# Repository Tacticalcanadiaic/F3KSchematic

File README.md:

# F3KSchematic
Schematic for ESP32-S3 flight unit for F3K

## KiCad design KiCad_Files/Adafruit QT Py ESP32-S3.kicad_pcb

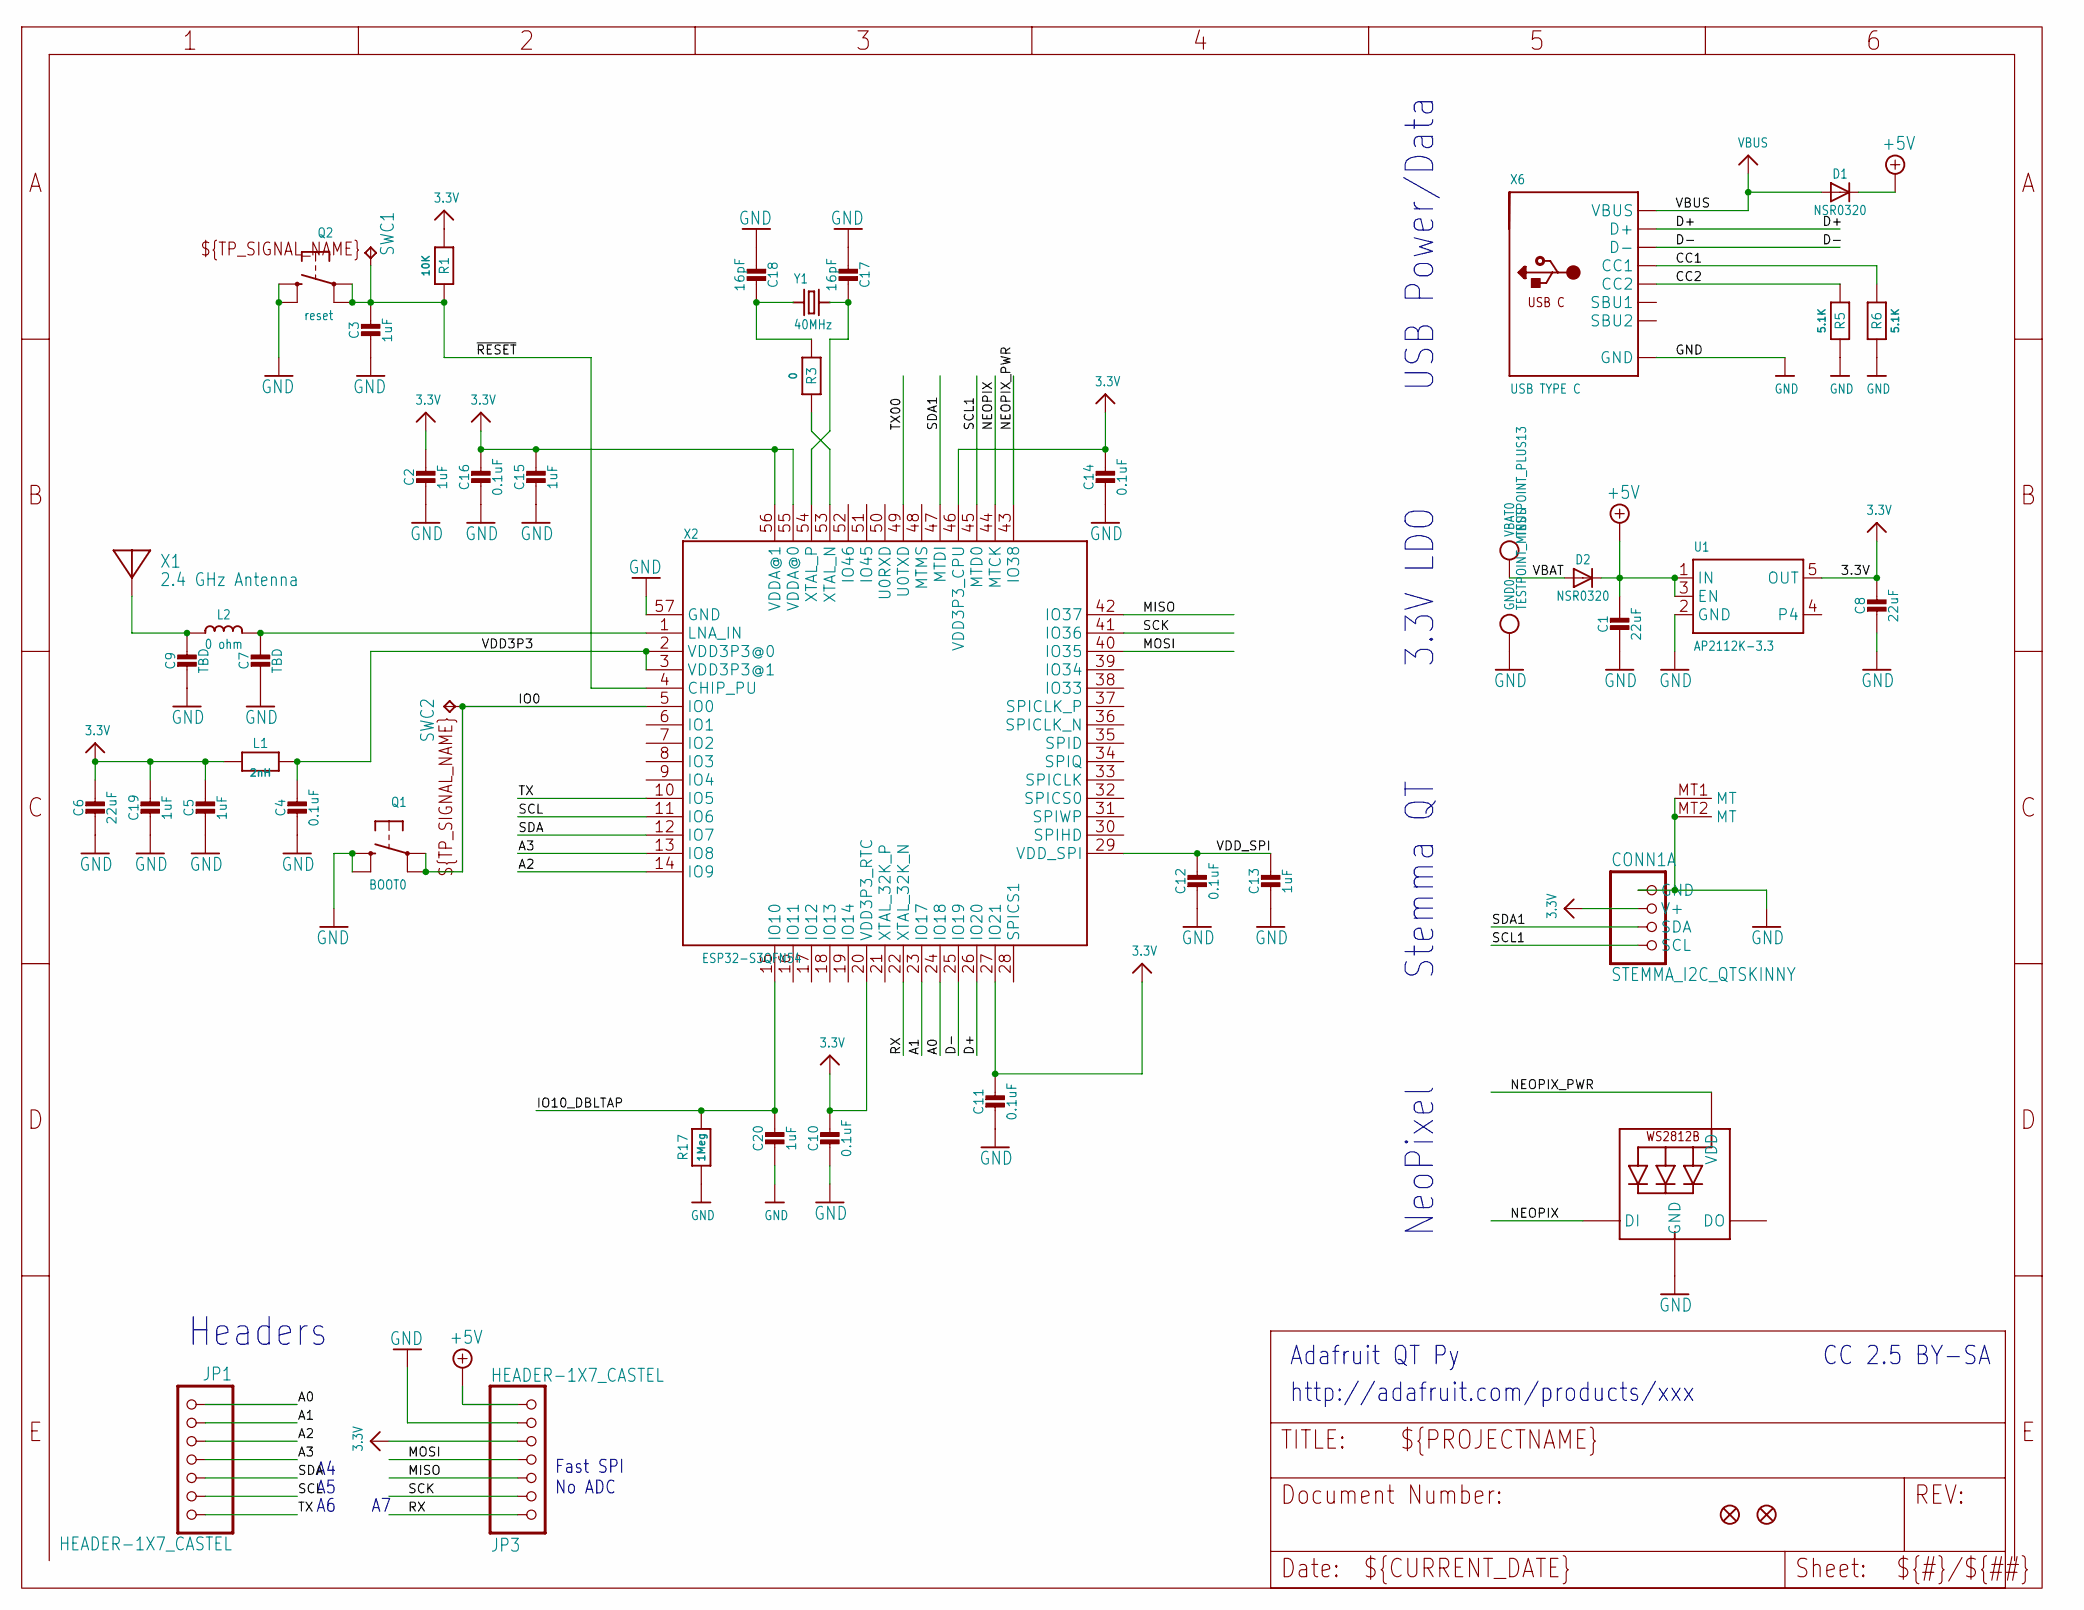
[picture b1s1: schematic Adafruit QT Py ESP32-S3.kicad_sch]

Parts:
C1, C6, C8: 22uF; 0805-NO
C2, C3, C5, C13, C15, C19, C20: 1uF; _0402NO
C4, C10, C11, C12, C14, C16: 0.1uF; _0402NO
C7, C9: TBD; _0402NO
C17, C18: 16pF; _0402NO
CONN1: STEMMA_I2C_QTSKINNY; JST_SH4_SKINNY
D1, D2: NSR0320; SOD-323_MINI
GND0: TESTPOINT_MINUS; TESTPOINT_MINUS_1X3MM
JP1, JP3: HEADER-1X7_CASTEL; 1X07_CASTEL
L1: 2nH; _0402NO
L2: 0 ohm; _0402
LED1: WS2812B_SK6805_1515; SK6805_1515
Q1: BOOT0; BTN_KMR2_4.6X2.8
Q2: reset; BTN_KMR2_4.6X2.8
R1: 10K; _0402NO
R3: 0; _0402NO
R5, R6: 5.1K; _0402NO
R17: 1Meg; _0402NO
SWC1, SWC2: TPB1,27; B1,27
U1: AP2112K-3.3; SOT23-5
U$6, U$8: FIDUCIAL_1MM
VBAT0: TESTPOINT_PLUS13; TESTPOINT_PLUS_1X3MM
X1: 2.4 GHz Antenna; ANT_2450AT18B100
X2: ESP32-S3QFN54; QFN56_7X7
X6: USB TYPE C; USB_C_CUSB31-CFM2AX-01-X
Y1: 40MHz; CRYSTAL_2X1.6

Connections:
3.3V: C2.1, C5.1, C6.1, C8.1, C10.1, C11.1, C14.1, C15.1, C16.1, C19.1, CONN1.2 (V+), JP3.5, JP3.5C (5), L1.1, R1.1, U1.5 (OUT), X2.20 (VDD3P3_RTC), X2.27 (IO21), X2.46 (VDD3P3_CPU), X2.55 (VDDA@0), X2.56 (VDDA@1)
+5V: C1.1, D1.C, D2.C, JP3.7, JP3.7C (7), U1.1 (IN), U1.3 (EN)
A0: JP1.1, JP1.1C (1), X2.24 (IO18)
A1: JP1.2, JP1.2C (2), X2.23 (IO17)
A2: JP1.3, JP1.3C (3), X2.14 (IO9)
A3: JP1.4, JP1.4C (4), X2.13 (IO8)
CC1: R6.2, X6.A5 (CC1)
CC2: R5.2, X6.B5 (CC2)
D+: X2.26 (IO20), X6.A6 (D+), X6.B6 (D+)
D-: X2.25 (IO19), X6.A7 (D-), X6.B7 (D-)
GND: C1.2, C2.2, C3.2, C4.2, C5.2, C6.2, C7.2, C8.2, C9.2, C10.2, C11.2, C12.2, C13.2, C14.2, C15.2, C16.2, C17.2, C18.2, C19.2, C20.2, CONN1.1 (GND), CONN1.MT1 (MT), CONN1.MT2 (MT), GND0.P$1, JP3.6, JP3.6C (6), LED1.4 (GND), Q1.B (S), Q1.B' (S1), Q2.B (S), Q2.B' (S1), R5.1, R6.1, R17.1, U1.2 (GND), X2.57 (GND), X6.A1B12 (GND), X6.B1A12 (GND)
IO0: Q1.A, Q1.A' (P1), SWC2.TP, X2.5 (IO0)
IO10_DBLTAP: C20.1, R17.2, X2.15 (IO10)
MISO: JP3.3, JP3.3C (3), X2.42 (IO37)
MOSI: JP3.4, JP3.4C (4), X2.40 (IO35)
unnamed: R3.2, X2.53 (XTAL_N)
unnamed: C7.1, L2.2, X2.1 (LNA_IN)
unnamed: C9.1, L2.1, X1.FP
unnamed: C17.1, X2.54 (XTAL_P), Y1.3 (2)
unnamed: C18.1, R3.1, Y1.1
NEOPIX: LED1.1 (DI), X2.44 (MTCK)
NEOPIX_PWR: LED1.2 (VDD), X2.43 (IO38)
RX: JP3.1, JP3.1C (1), X2.22 (XTAL_32K_N)
SCK: JP3.2, JP3.2C (2), X2.41 (IO36)
SCL: JP1.6, JP1.6C (6), X2.11 (IO6)
SCL1: CONN1.4 (SCL), X2.45 (MTD0)
SDA: JP1.5, JP1.5C (5), X2.12 (IO7)
SDA1: CONN1.3 (SDA), X2.47 (MTDI)
TX: JP1.7, JP1.7C (7), X2.10 (IO5)
TX00: X2.49 (U0TXD)
VBAT: D2.A, VBAT0.P$1
VBUS: D1.A, X6.A4B9 (VBUS), X6.B4A9 (VBUS)
VDD3P3: C4.1, L1.2, X2.2 (VDD3P3@0), X2.3 (VDD3P3@1)
VDD_SPI: C12.1, C13.1, X2.29 (VDD_SPI)
~RESET: C3.1, Q2.A, Q2.A' (P1), R1.2, SWC1.TP, X2.4 (CHIP_PU)

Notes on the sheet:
CC 2.5 BY-SA
NeoPixel
USB Power/Data
http://adafruit.com/products/xxx
Adafruit QT Py
3.3V LDO
Stemma QT
Headers
Fast SPI No ADC

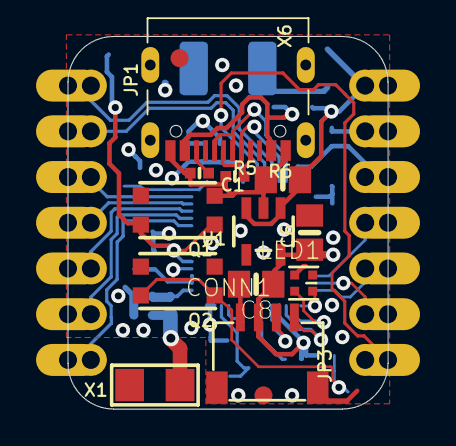
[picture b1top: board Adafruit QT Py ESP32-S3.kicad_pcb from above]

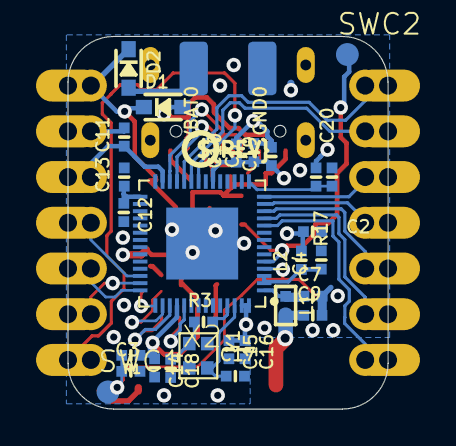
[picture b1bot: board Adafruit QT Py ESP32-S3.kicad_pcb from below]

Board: 4 copper layers, 17.8 x 20.7 mm, 49 parts (32 on the bottom side), 34 nets.

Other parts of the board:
U$7: QTPY_ESP32_TOP
U$11: QTPYS3_BOT
U$12: PCBFEAT-REV-040

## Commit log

2026-06-04 added schematic
2026-06-04 added spreadsheet
2026-06-04 reorganized files
2026-06-04 added components
2026-06-04 added
2026-06-04 added esp32-s3 schematic and pcb files, organized kicad hierarchy
2026-06-13 added RAK, confusion on USB pins
